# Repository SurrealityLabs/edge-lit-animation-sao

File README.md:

# edge-lit-animation-sao
Edge Lit Animation SAO

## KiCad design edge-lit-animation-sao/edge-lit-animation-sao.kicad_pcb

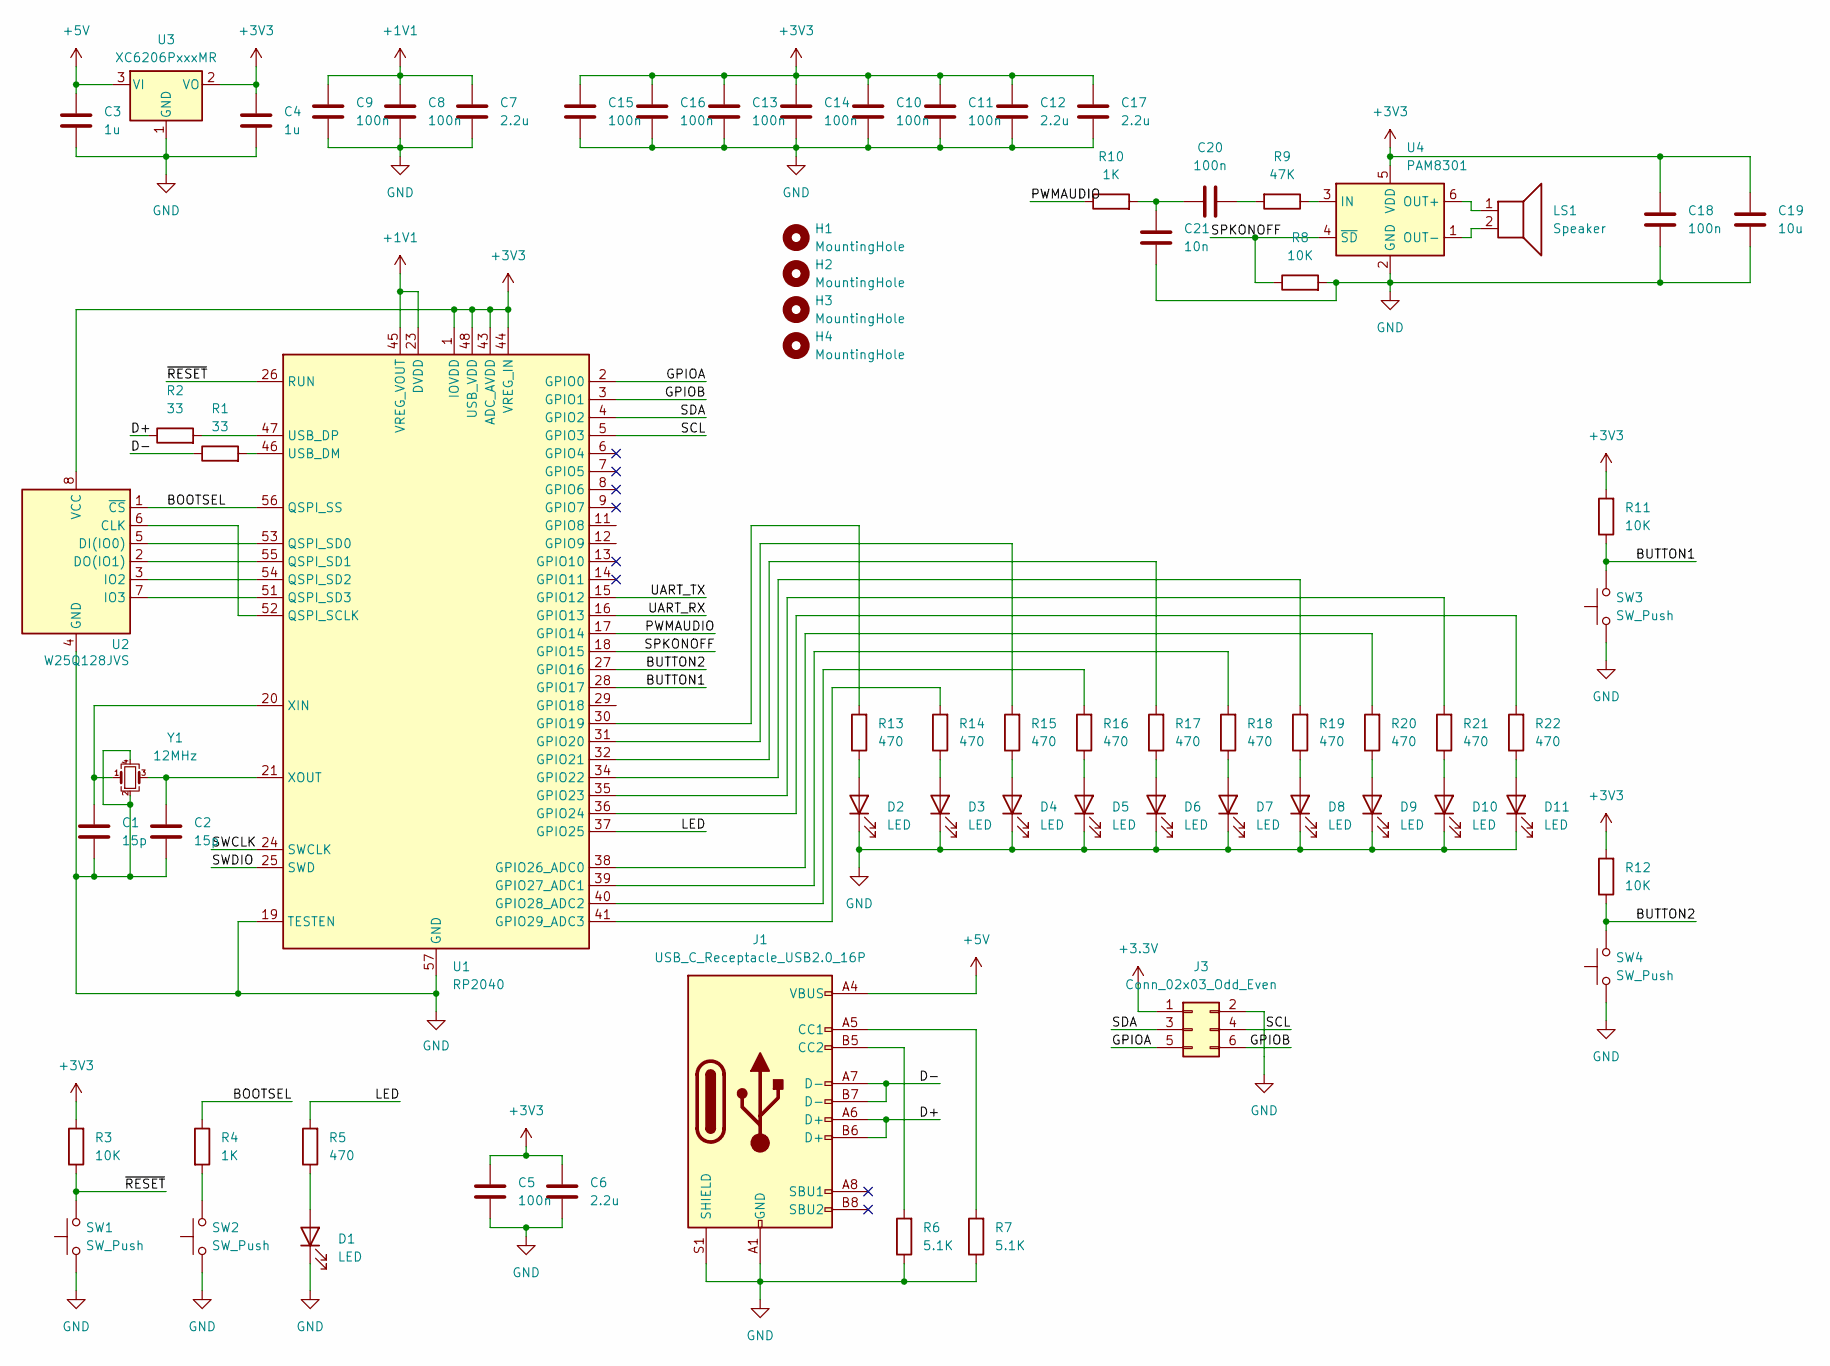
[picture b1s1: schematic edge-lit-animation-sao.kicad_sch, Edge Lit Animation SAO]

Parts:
C1, C2: 15p; C_0402_1005Metric; LCSC C1548
C3, C4: 1u; C_0402_1005Metric; LCSC C52923
C5, C8, C9, C10, C11, C13, C14, C15, C16, C18, C20: 100n; C_0402_1005Metric; LCSC C307331
C6, C7, C12, C17: 2.2u; C_0603_1608Metric; LCSC C23630
C19: 10u; C_0805_2012Metric; LCSC C440198
C21: 10n; C_0402_1005Metric; LCSC C15195
D1: LED; LED_0603_1608Metric; LCSC C2286
D2, D3, D4, D5, D6, D7, D8, D9, D10, D11: LED; LED_0805_2012Metric_Pad1.15x1.40mm_HandSolder; LCSC C34499
H1, H2, H3, H4: MountingHole; MountingHole_3.2mm_M3_DIN965
J1: USB_C_Receptacle_USB2.0_16P; USB_C_Receptacle_HRO_TYPE-C-31-M-12; LCSC C165948
J3: Conn_02x03_Odd_Even; IDC-Header_2x03_P2.54mm_Horizontal
LS1: Speaker; CUI_CMT-8530S-SMT; LCSC C94599
R1, R2: 33; R_0402_1005Metric; LCSC C97521
R3, R8, R11, R12: 10K; R_0402_1005Metric; LCSC C25744
R4, R10: 1K; R_0402_1005Metric; LCSC C11702
R5, R13, R14, R15, R16, R17, R18, R19, R20, R21, R22: 470; R_0402_1005Metric; LCSC C25517
R6, R7: 5.1K; R_0402_1005Metric; LCSC C25905
R9: 47K; R_0402_1005Metric; LCSC C25792
SW1, SW2, SW3, SW4: SW_Push; SW_Push_1P1T_XKB_TS-1187A; LCSC C318884
U1: RP2040; QFN-56-1EP_7x7mm_P0.4mm_EP3.2x3.2mm; LCSC C2040
U2: W25Q128JVS; SOIC-8_5.23x5.23mm_P1.27mm; LCSC C113767
U3: XC6206PxxxMR; SOT-23-3; LCSC C5446
U4: PAM8301; SOT-23-6; LCSC C3001605
Y1: 12MHz; Crystal_SMD_3225-4Pin_3.2x2.5mm; LCSC C3003246

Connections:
+1V1: C7.1, C8.1, C9.1, U1.23 (DVDD), U1.45 (VREG_VOUT), U1.50 (DVDD)
+3.3V: J3.1
+3V3: C4.1, C5.1, C6.1, C10.1, C11.1, C12.1, C13.1, C14.1, C15.1, C16.1, C17.1, C18.1, C19.1, R3.2, R11.2, R12.2, U1.1 (IOVDD), U1.10 (IOVDD), U1.22 (IOVDD), U1.33 (IOVDD), U1.42 (IOVDD), U1.43 (ADC_AVDD), U1.44 (VREG_IN), U1.48 (USB_VDD), U1.49 (IOVDD), U2.8 (VCC), U3.2 (VO), U4.5 (VDD)
+5V: C3.1, J1.A4 (VBUS), J1.A9 (VBUS), J1.B4 (VBUS), J1.B9 (VBUS), U3.3 (VI)
/BOOTSEL: R4.1, U1.56 (QSPI_SS), U2.1 (~CS)
/BUTTON1: R11.1, SW3.2, U1.28 (GPIO17)
/BUTTON2: R12.1, SW4.2, U1.27 (GPIO16)
/D+: J1.A6 (D+), J1.B6 (D+), R2.1
/D-: J1.A7 (D-), J1.B7 (D-), R1.1
/GPIOA: J3.5, U1.2 (GPIO0)
/GPIOB: J3.6, U1.3 (GPIO1)
/LED: R5.2, U1.37 (GPIO25)
/PWMAUDIO: R10.1, U1.17 (GPIO14)
/SCL: J3.4, U1.5 (GPIO3)
/SDA: J3.3, U1.4 (GPIO2)
/SPKONOFF: R8.1, U1.18 (GPIO15), U4.4 (~SD)
/SWCLK: U1.24 (SWCLK)
/SWDIO: U1.25 (SWD)
/UART_RX: U1.16 (GPIO13)
/UART_TX: U1.15 (GPIO12)
/~RESET: R3.1, SW1.2, U1.26 (RUN)
GND: C1.2, C2.2, C3.2, C4.2, C5.2, C6.2, C7.2, C8.2, C9.2, C10.2, C11.2, C12.2, C13.2, C14.2, C15.2, C16.2, C17.2, C18.2, C19.2, C21.2, D1.1 (K), D2.1 (K), D3.1 (K), D4.1 (K), D5.1 (K), D6.1 (K), D7.1 (K), D8.1 (K), D9.1 (K), D10.1 (K), D11.1 (K), J1.A1 (GND), J1.A12 (GND), J1.B1 (GND), J1.B12 (GND), J1.S1 (SHIELD), J3.2, R6.1, R7.1, R8.2, SW1.1, SW2.1, SW3.1, SW4.1, U1.19 (TESTEN), U1.57 (GND), U2.4 (GND), U3.1 (GND), U4.2 (GND), Y1.2, Y1.4
unnamed: C20.1, C21.1, R10.2
unnamed: C20.2, R9.2
unnamed: D1.2 (A), R5.1
unnamed: D2.2 (A), R13.1
unnamed: D3.2 (A), R14.1
unnamed: D4.2 (A), R15.1
unnamed: D5.2 (A), R16.1
unnamed: D6.2 (A), R17.1
unnamed: D7.2 (A), R18.1
unnamed: D8.2 (A), R19.1
unnamed: D9.2 (A), R20.1
unnamed: D10.2 (A), R21.1
unnamed: D11.2 (A), R22.1
unnamed: J1.A5 (CC1), R7.2
unnamed: J1.B5 (CC2), R6.2
unnamed: R4.2, SW2.2
unnamed: R13.2, U1.30 (GPIO19)
unnamed: R15.2, U1.31 (GPIO20)
unnamed: R17.2, U1.32 (GPIO21)
unnamed: R19.2, U1.34 (GPIO22)
unnamed: R21.2, U1.35 (GPIO23)
unnamed: R22.2, U1.36 (GPIO24)
unnamed: R20.2, U1.38 (GPIO26_ADC0)
unnamed: R18.2, U1.39 (GPIO27_ADC1)
unnamed: R16.2, U1.40 (GPIO28_ADC2)
unnamed: R14.2, U1.41 (GPIO29_ADC3)
unnamed: U1.52 (QSPI_SCLK), U2.6 (CLK)
unnamed: U1.53 (QSPI_SD0), U2.5 (DI(IO0))
unnamed: U1.55 (QSPI_SD1), U2.2 (DO(IO1))
unnamed: U1.54 (QSPI_SD2), U2.3 (IO2)
unnamed: U1.51 (QSPI_SD3), U2.7 (IO3)
unnamed: R1.2, U1.46 (USB_DM)
unnamed: R2.2, U1.47 (USB_DP)
unnamed: C1.1, U1.20 (XIN), Y1.1
unnamed: C2.1, U1.21 (XOUT), Y1.3
unnamed: R9.1, U4.3 (IN)
unnamed: LS1.1, U4.6 (OUT+)
unnamed: LS1.2, U4.1 (OUT-)

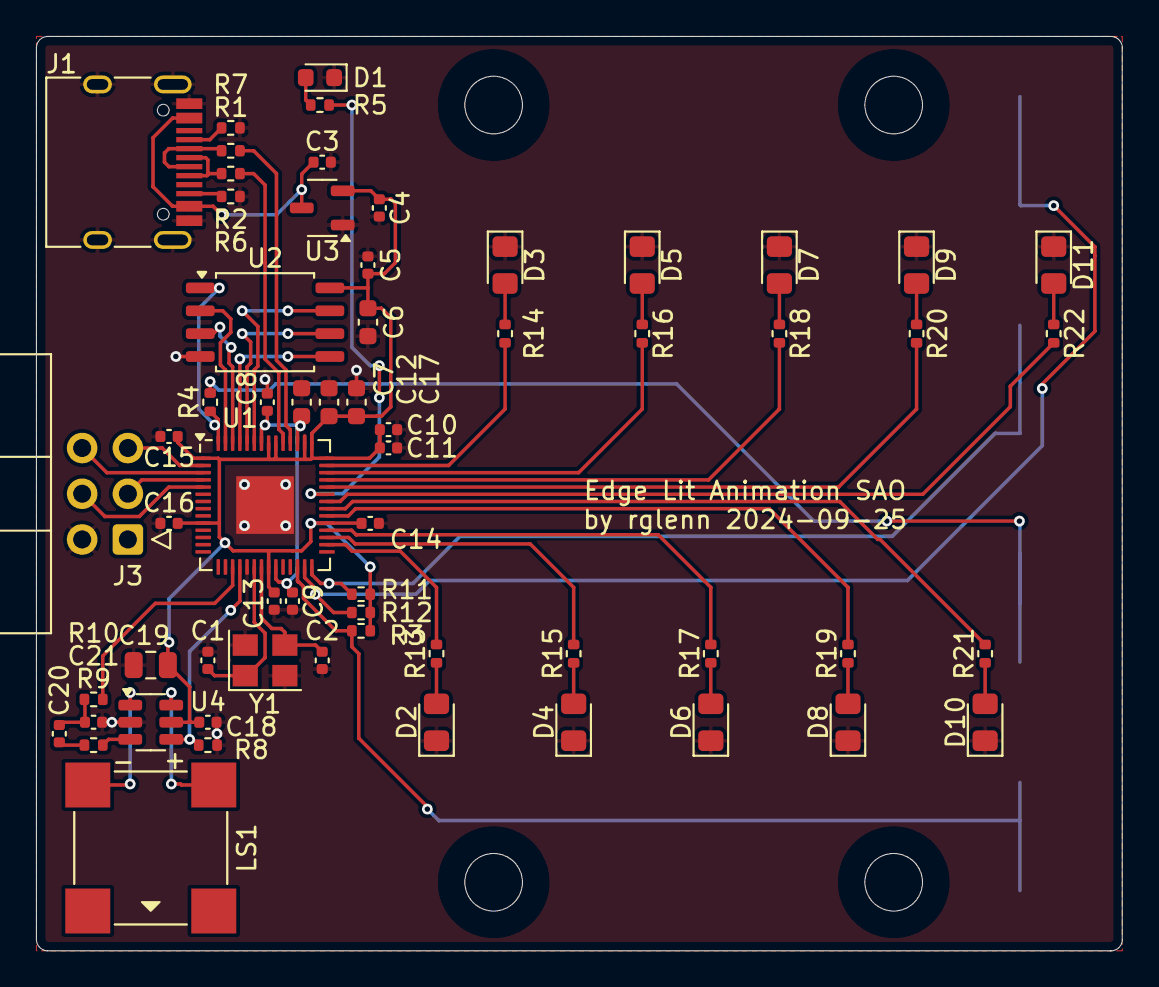
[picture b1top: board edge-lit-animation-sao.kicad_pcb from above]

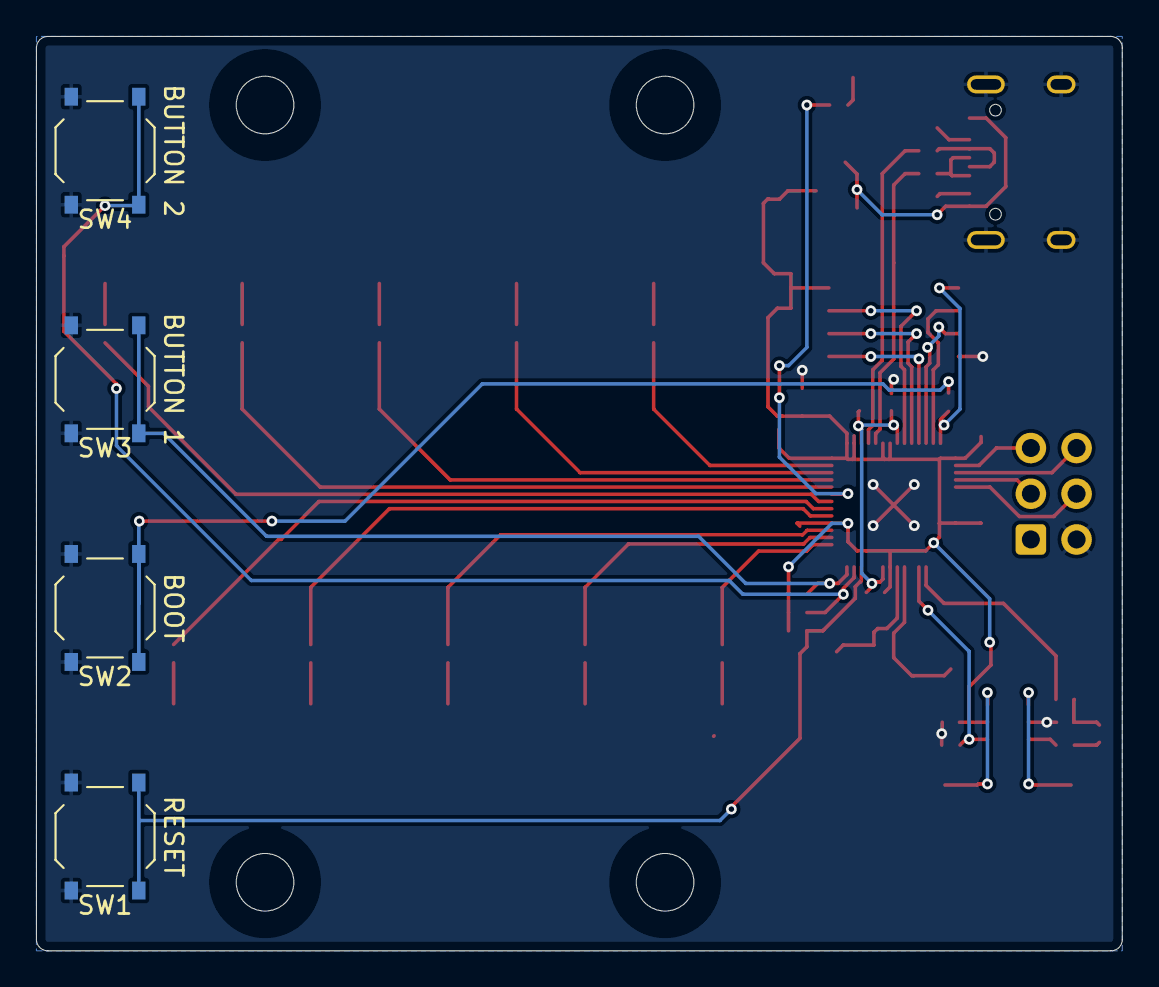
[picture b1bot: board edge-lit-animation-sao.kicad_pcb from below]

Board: 2 copper layers, 60.3 x 50.8 mm, 70 parts (4 on the bottom side), 55 nets.

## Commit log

2024-08-25 Adding PCB layout for SAO
2024-08-29 Changing from WS2812s to standard white LEDs
